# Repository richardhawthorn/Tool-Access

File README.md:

### Features

- Particle Photon
- 10A relay
- Current sensing
- RTC with battery backup
- Temperature input
- 3 x external inputs
- RFID reader connector
- 3.3V operation
- Onboard transformer 110v -> 5v

### License

This work is licensed under a Creative Commons Attribution-ShareAlike 4.0 International License.

<br />
Designed by <a xmlns:cc="http://creativecommons.org/ns#" href="http://www.richardhawthorn.com" property="cc:attributionName" rel="cc:attributionURL" target="_blank">Richard Hawthorn</a><br />
<a rel="license" href="http://creativecommons.org/licenses/by-sa/4.0/" target="_blank">View License</a>

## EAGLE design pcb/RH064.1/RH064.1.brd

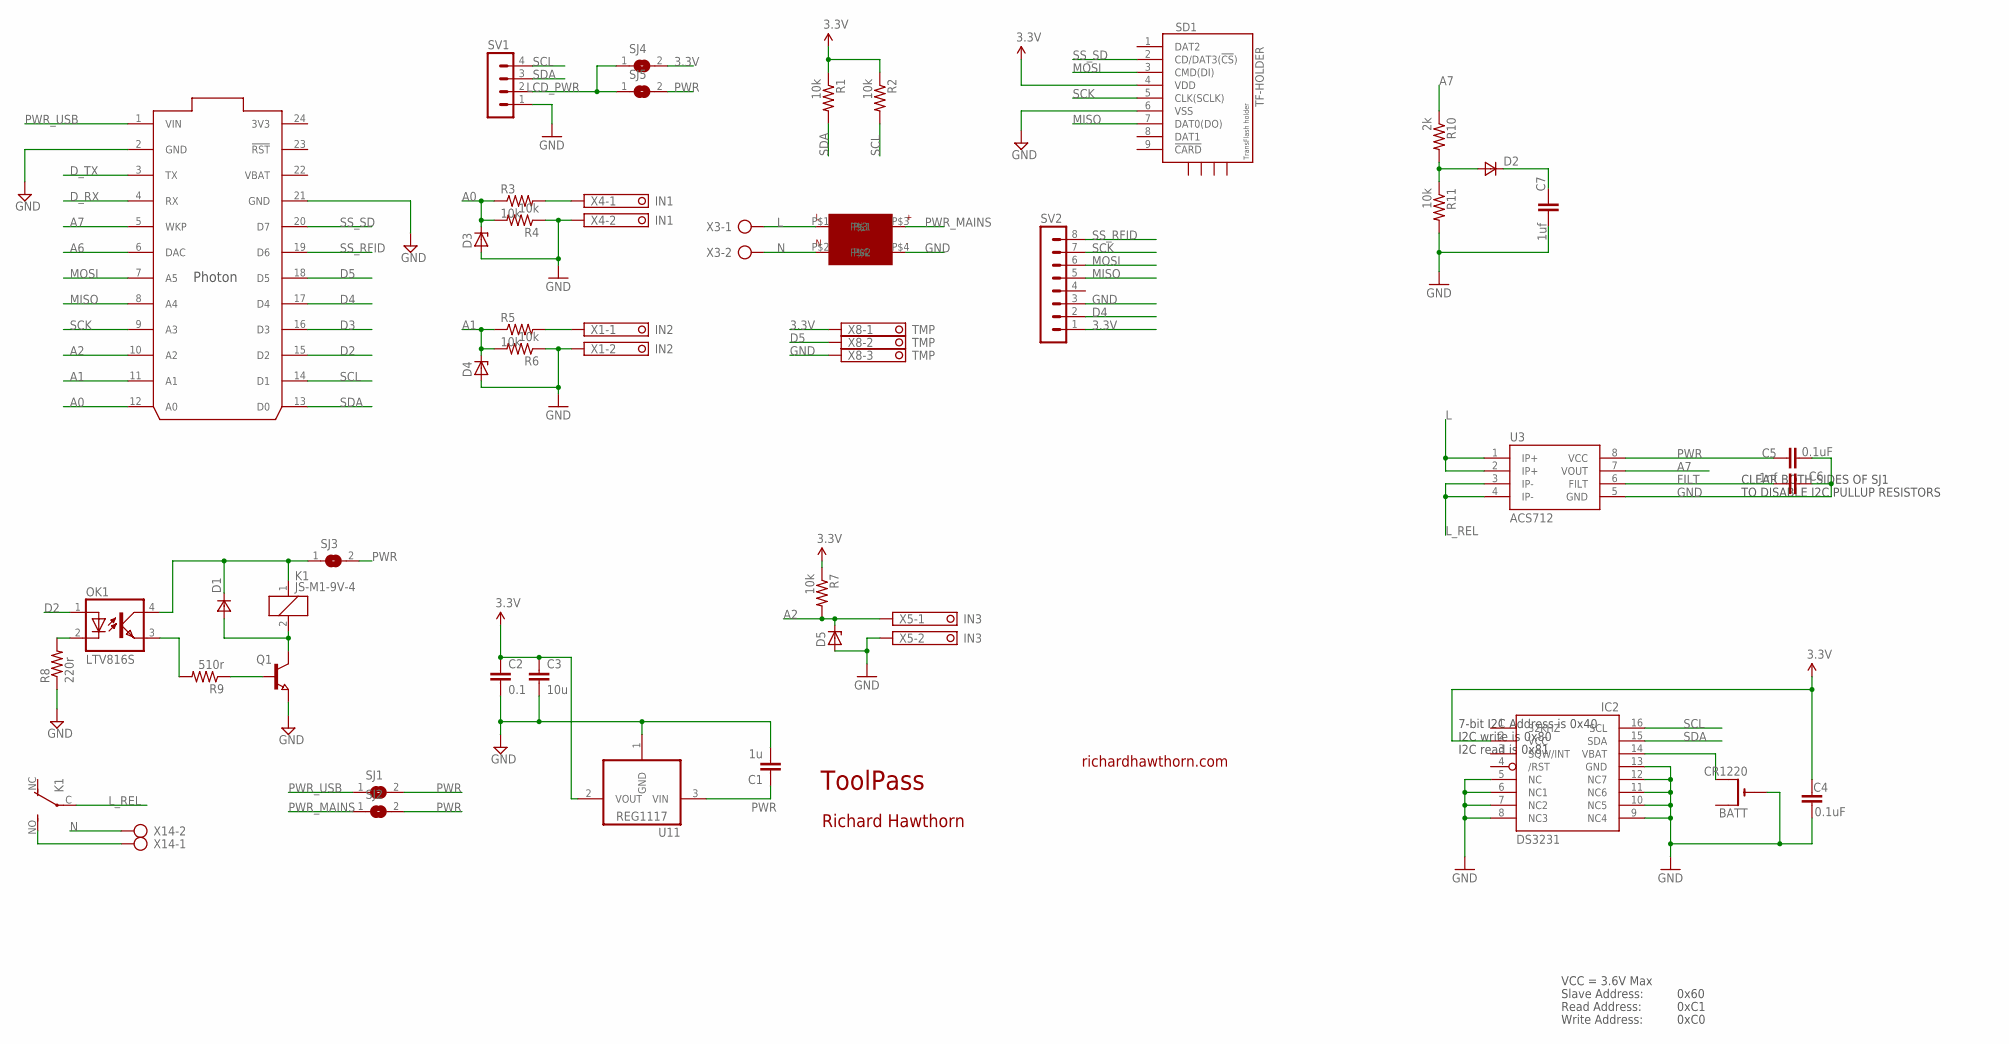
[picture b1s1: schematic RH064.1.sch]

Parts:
BATT: CR1220; CR1220-SMD
C1: 1u; 0603-CAP
C2: 0.1; 0603-CAP
C3: 10u; 0805-CAP
C4, C5: 0.1uF; 0603-CAP
C6: 1nf; 0603-CAP
C7: 1uf; 0603-CAP
D1, D2: VAR2SOT23; SOT-23
D3, D4, D5: ZENER-DIODESOT23; SOT23
IC2: DS3231; SO16W
K1: JS-M1-9V-4; JS-M
OK1: LTV816S; SMD4
Q1: NPN-TRANSISTOR_SOT23; SOT23
R1, R2, R11: 10k; 0805
R3, R4, R5, R6, R7: 10k; 0603-RES
R8: 220r; 0603-RES
R9: 510r; 0603-RES
R10: 2k; 0805
SD1: TF-HOLDER; TF-PULL
SJ1, SJ2, SJ3, SJ4, SJ5: SJ
SV1: MA04-1
SV2: MA08-1
U1: PHOTON_SMD
U3: ACS712; SO08
U11: REG1117; SOT223
U$1: 5VPWR
X1: IN2; 1751248
X3, X14: AK500/2
X4: IN1; 1751248
X5: IN3; 1751248
X8: TMP; 1751251

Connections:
3.3V: C2.1, C3.1, C4.1, IC2.2 (VCC), R1.1, R2.1, R7.1, SD1.4 (VDD), SJ4.2, SV2.1, U11.2 (VOUT), X8.1
3V3: U1.24 (3V3)
A0: D3.3 (C), R3.1, R4.2, U1.12 (A0)
A1: D4.3 (C), R5.1, R6.2, U1.11 (A1)
A2: D5.3 (C), R7.2, U1.10 (A2), X5.1
A6: U1.6 (DAC)
A7: R10.1, U1.5 (WKP), U3.7 (VOUT)
D2: OK1.1 (A), U1.15 (D2)
D3: U1.16 (D3)
D4: SV2.2, U1.17 (D4)
D5: U1.18 (D5), X8.2
D_RX: U1.4 (RX)
D_TX: U1.3 (TX)
FILT: C6.2, U3.6 (FILT)
GND: BATT.-, C1.2, C2.2, C3.2, C4.2, C5.2, C6.1, C7.2, D3.1 (A), D4.1 (A), D5.1 (A), IC2.5 (NC), IC2.6 (NC1), IC2.7 (NC2), IC2.8 (NC3), IC2.9 (NC4), IC2.10 (NC5), IC2.11 (NC6), IC2.12 (NC7), IC2.13 (GND), Q1.2 (E), R4.1, R6.1, R8.1, R11.2, SD1.6 (VSS), SV1.1, SV2.3, U1.2 (GND), U1.21 (GND), U3.5 (GND), U11.1 (GND), U$1.P$4, X1.2, X4.2, X5.2, X8.3
L: U3.1 (IP+), U3.2 (IP+), U$1.P$1, X3.1
LCD_PWR: SJ4.1, SJ5.1, SV1.2
L_REL: K1.C, U3.3 (IP-), U3.4 (IP-)
MISO: SD1.7 (DAT0(DO)), SV2.5, U1.8 (A4)
MOSI: SD1.3 (CMD(DI)), SV2.6, U1.7 (A5)
N: U$1.P$2, X3.2, X14.2
unnamed: OK1.3 (EMIT), R9.2
unnamed: R5.2, X1.1
unnamed: OK1.2 (C), R8.2
unnamed: K1.NO (S), X14.1
unnamed: R3.2, X4.1
unnamed: Q1.1 (B), R9.1
unnamed: D1.3 (A), K1.2, Q1.3 (C)
unnamed: BATT.+$2 (+1), IC2.14 (VBAT)
unnamed: D2.3 (A), R10.2, R11.1
unnamed: C7.1, D2.1 (C)
PWR: C1.1, C5.1, SJ1.2, SJ2.2, SJ3.2, SJ5.2, U3.8 (VCC), U11.3 (VIN)
PWR_MAINS: SJ2.1, U$1.P$3
PWR_USB: SJ1.1, U1.1 (VIN)
RL_PWR: D1.1 (C), K1.1, OK1.4 (COL), SJ3.1
SCK: SD1.5 (CLK(SCLK)), SV2.7, U1.9 (A3)
SCL: IC2.16 (SCL), R2.2, SV1.4, U1.14 (D1)
SDA: IC2.15 (SDA), R1.2, SV1.3, U1.13 (D0)
SS_RFID: SV2.8, U1.19 (D6)
SS_SD: SD1.2 (CD/DAT3(!CS!)), U1.20 (D7)
VBAT: U1.22 (VBAT)

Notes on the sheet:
ToolPass
richardhawthorn.com
Richard Hawthorn
CLEAR BOTH SIDES OF SJ1
TO DISABLE I2C PULLUP RESISTORS
7-bit I2C Address is 0x40
I2C write is 0x80
I2C read is 0x81
VCC = 3.6V Max
Read Address:
Write Address:
Slave Address:
0x60
0xC1
0xC0

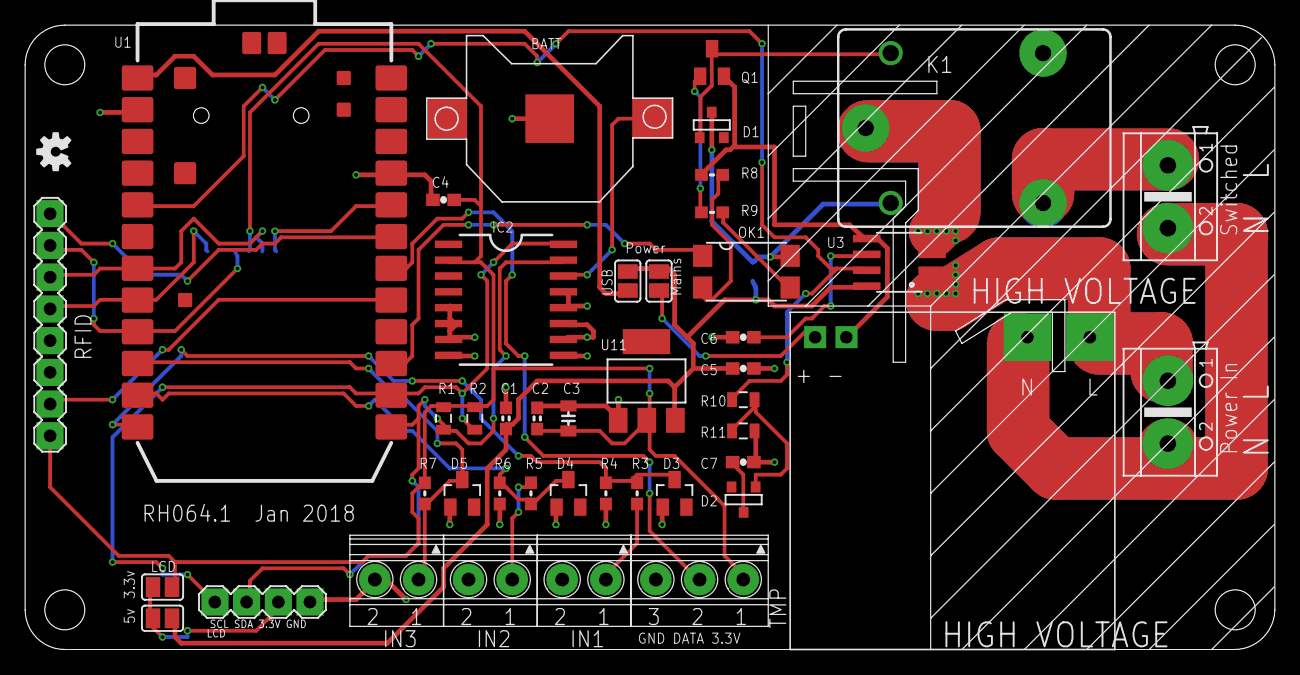
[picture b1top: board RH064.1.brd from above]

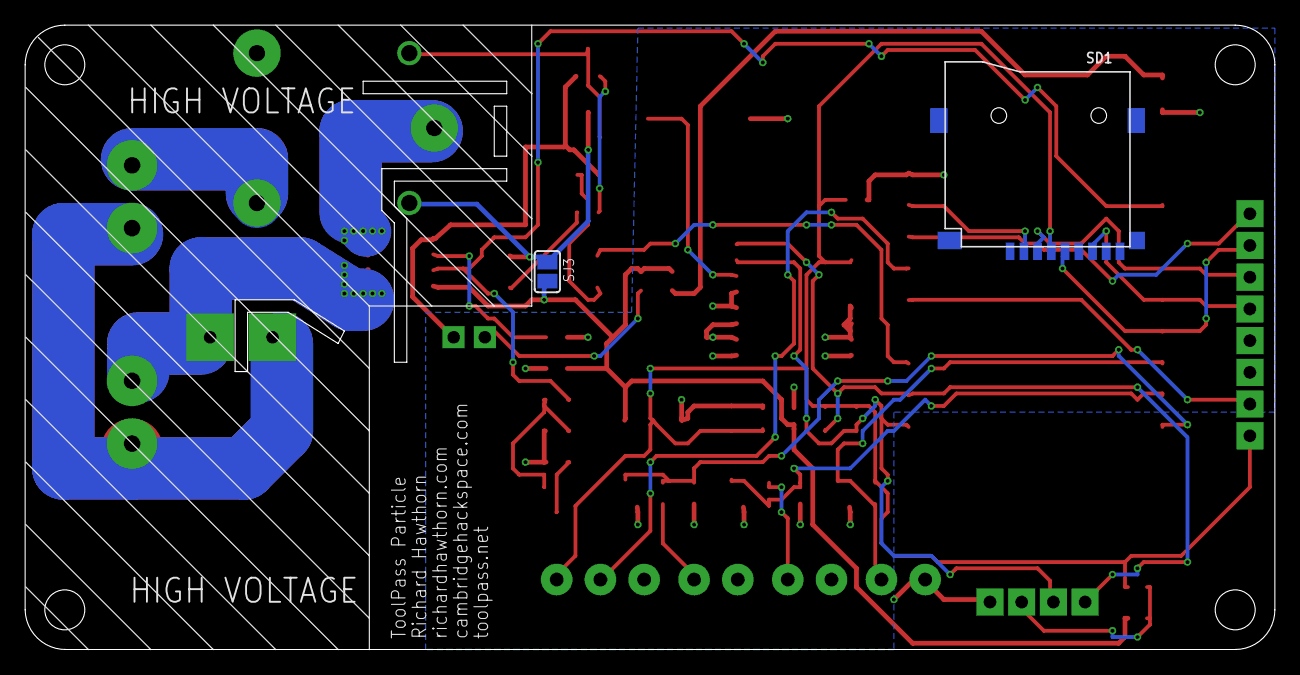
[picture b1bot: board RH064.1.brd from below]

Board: 2 copper layers, 100.1 x 50.0 mm, 47 parts (2 on the bottom side), 35 nets.

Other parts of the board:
U$3: OSHW-LOGO-S

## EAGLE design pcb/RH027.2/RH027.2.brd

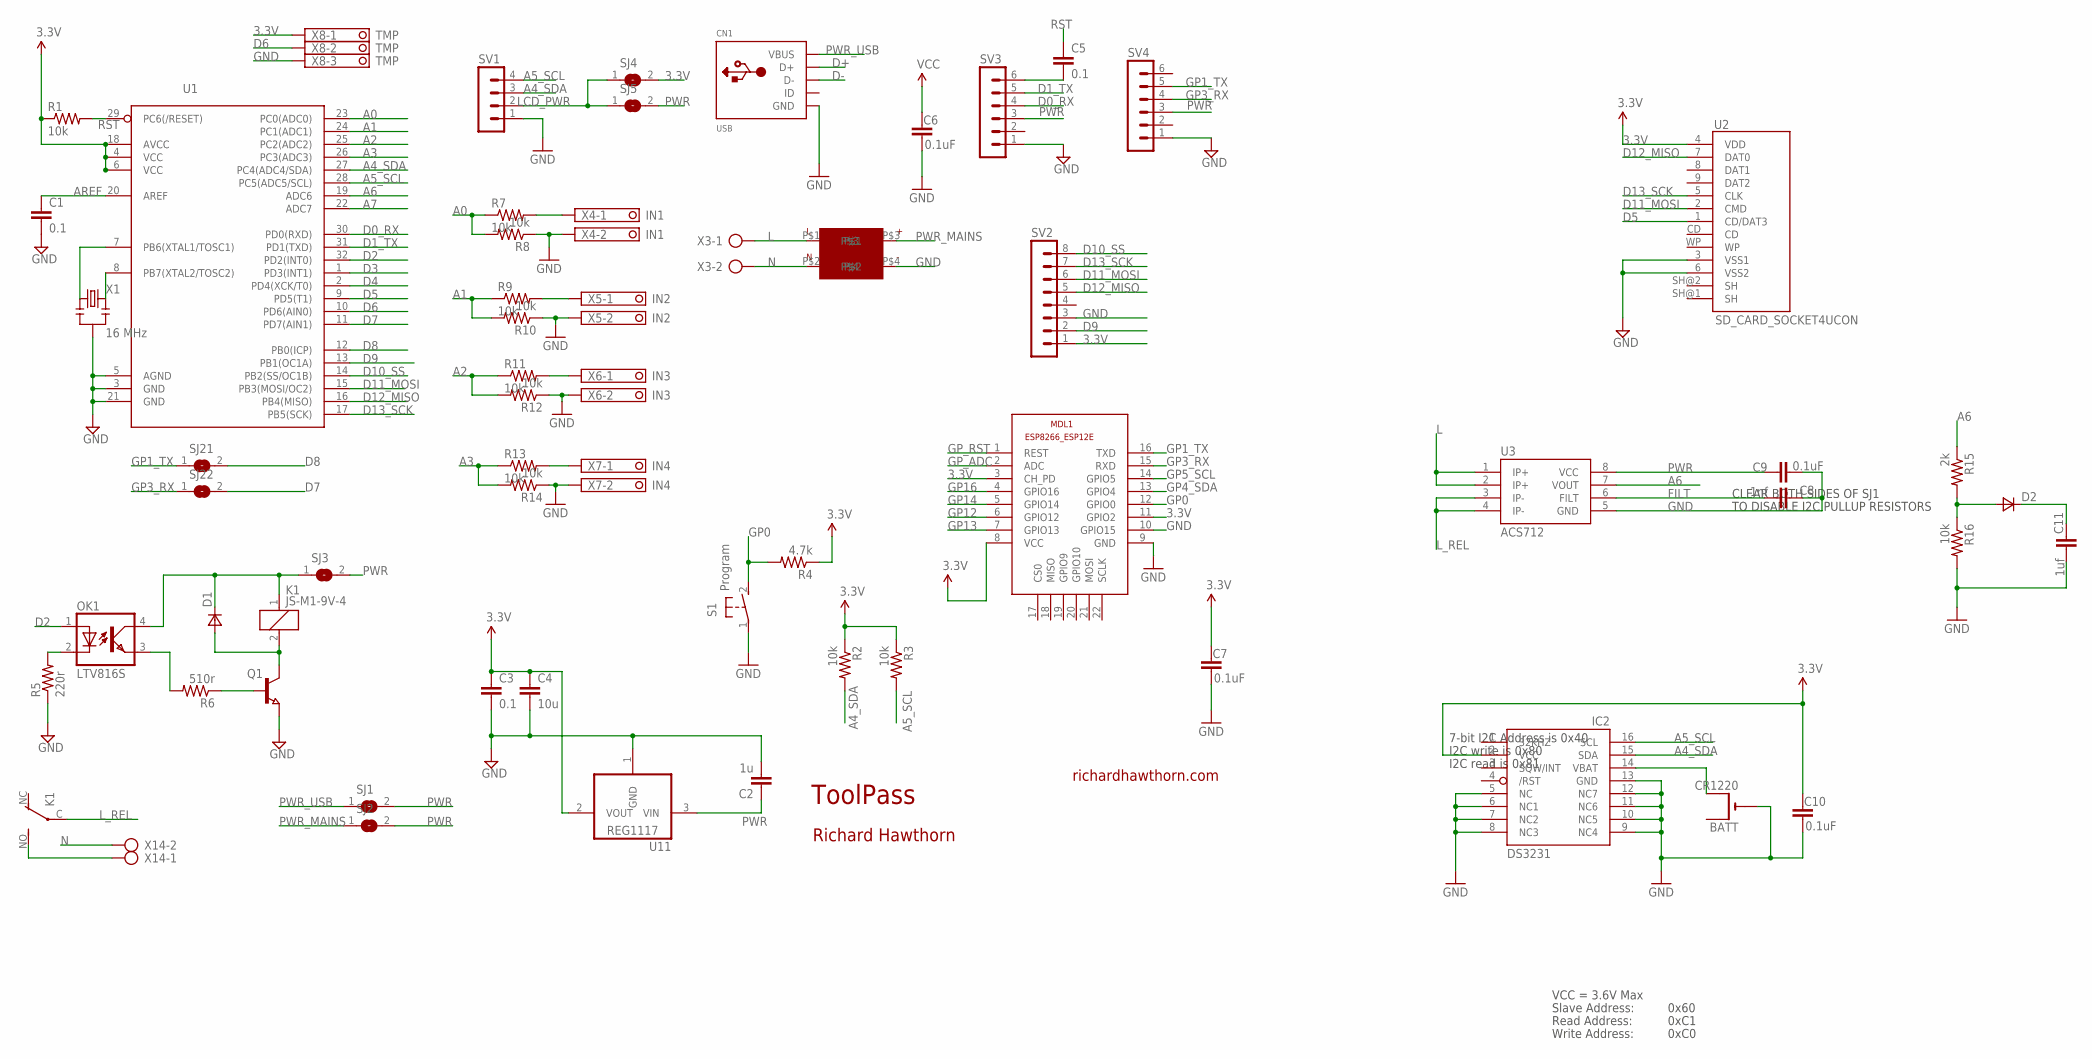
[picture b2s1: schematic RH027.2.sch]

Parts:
BATT: CR1220; CR1220-SMD
C1, C3, C5: 0.1; 0603-CAP
C2: 1u; 0603-CAP
C4: 10u; 0805-CAP
C6, C7, C9, C10: 0.1uF; 0603-CAP
C8: 1nf; 0603-CAP
C11: 1uf; 0603-CAP
CN1: USB; USB-MINIB
D1, D2: VAR2SOT23; SOT-23
IC2: DS3231; SO16W
K1: JS-M1-9V-4; JS-M
MDL1: ESP8266-12EESP8266-ESP12E; ESP8266-ESP12E
OK1: LTV816S; SMD4
Q1: NPN-TRANSISTOR_SOT23; SOT23
R1, R7, R8, R9, R10, R11, R12, R13, R14: 10k; 0603-RES
R2, R3, R16: 10k; 0805
R4: 4.7k; 0805
R5: 220r; 0603-RES
R6: 510r; 0603-RES
R15: 2k; 0805
S1: Program; DTSM-3
SJ1, SJ2, SJ3, SJ4, SJ5, SJ21, SJ22: SJ
SV1: MA04-1
SV2: MA08-1
SV3, SV4: MA06-1
U1: ATMega-328; TQFP32-08
U2: SD_CARD_SOCKET4UCON; SDCARD_4UCONN
U3: ACS712; SO08
U11: REG1117; SOT223
U$1: 5VPWR
X1: 16 MHz; RESONATOR-SMD
X3, X14: AK500/2
X4: IN1; 1751248
X5: IN2; 1751248
X6: IN3; 1751248
X7: IN4; 1751248
X8: TMP; 1751251

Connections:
3.3V: C3.1, C4.1, C6.1, C7.1, C10.1, IC2.2 (VCC), MDL1.3 (CH_PD), MDL1.8 (VCC), MDL1.11 (GPIO2), R1.1, R2.1, R3.1, R4.1, SJ4.2, SV2.1, U1.4 (VCC), U1.6 (VCC), U1.18 (AVCC), U2.4 (VDD), U11.2 (VOUT), X8.1
A0: R7.1, R8.2, U1.23 (PC0(ADC0))
A1: R9.1, R10.2, U1.24 (PC1(ADC1))
A2: R11.1, R12.2, U1.25 (PC2(ADC2))
A3: R13.1, R14.2, U1.26 (PC3(ADC3))
A4_SDA: IC2.15 (SDA), R2.2, SV1.3, U1.27 (PC4(ADC4/SDA))
A5_SCL: IC2.16 (SCL), R3.2, SV1.4, U1.28 (PC5(ADC5/SCL))
A6: R15.1, U1.19 (ADC6), U3.7 (VOUT)
A7: U1.22 (ADC7)
AREF: C1.1, U1.20 (AREF)
D0_RX: SV3.4, U1.30 (PD0(RXD))
D1_TX: SV3.5, U1.31 (PD1(TXD))
D2: OK1.1 (A), U1.32 (PD2(INT0))
D3: U1.1 (PD3(INT1))
D4: U1.2 (PD4(XCK/T0))
D5: U1.9 (PD5(T1)), U2.1 (CD/DAT3)
D6: U1.10 (PD6(AIN0)), X8.2
D7: SJ22.2, U1.11 (PD7(AIN1))
D8: SJ21.2, U1.12 (PB0(ICP))
D9: SV2.2, U1.13 (PB1(OC1A))
D10_SS: SV2.8, U1.14 (PB2(SS/OC1B))
D11_MOSI: SV2.6, U1.15 (PB3(MOSI/OC2)), U2.2 (CMD)
D12_MISO: SV2.5, U1.16 (PB4(MISO)), U2.7 (DAT0)
D13_SCK: SV2.7, U1.17 (PB5(SCK)), U2.5 (CLK)
D+: CN1.D+
D-: CN1.D-
FILT: C8.2, U3.6 (FILT)
GND: BATT.-, C1.2, C2.2, C3.2, C4.2, C6.2, C7.2, C8.1, C9.2, C10.2, C11.2, CN1.GND, IC2.5 (NC), IC2.6 (NC1), IC2.7 (NC2), IC2.8 (NC3), IC2.9 (NC4), IC2.10 (NC5), IC2.11 (NC6), IC2.12 (NC7), IC2.13 (GND), MDL1.9 (GND), MDL1.10 (GPIO15), Q1.2 (E), R5.1, R8.1, R10.1, R12.1, R14.1, R16.2, S1.1, SV1.1, SV2.3, SV3.1, SV4.1, U1.3 (GND), U1.5 (AGND), U1.21 (GND), U2.3 (VSS1), U2.6 (VSS2), U3.5 (GND), U11.1 (GND), U$1.P$4, X1.2, X4.2, X5.2, X6.2, X7.2, X8.3
GP0: MDL1.12 (GPIO0), R4.2, S1.2
GP1_TX: MDL1.16 (TXD), SJ21.1, SV4.5
GP3_RX: MDL1.15 (RXD), SJ22.1, SV4.4
GP4_SDA: MDL1.13 (GPIO4)
GP5_SCL: MDL1.14 (GPIO5)
GP12: MDL1.6 (GPIO12)
GP13: MDL1.7 (GPIO13)
GP14: MDL1.5 (GPIO14)
GP16: MDL1.4 (GPIO16)
GP_ADC: MDL1.2 (ADC)
GP_RST: MDL1.1 (REST)
L: U3.1 (IP+), U3.2 (IP+), U$1.P$1, X3.1
LCD_PWR: SJ4.1, SJ5.1, SV1.2
L_REL: K1.C, U3.3 (IP-), U3.4 (IP-)
N: U$1.P$2, X3.2, X14.2
unnamed: OK1.3 (EMIT), R6.2
unnamed: U1.7 (PB6(XTAL1/TOSC1)), X1.1
unnamed: OK1.2 (C), R5.2
unnamed: K1.NO (S), X14.1
unnamed: R9.2, X5.1
unnamed: R7.2, X4.1
unnamed: R11.2, X6.1
unnamed: R13.2, X7.1
unnamed: C5.2, SV3.6
unnamed: U1.8 (PB7(XTAL2/TOSC2)), X1.3
unnamed: Q1.1 (B), R6.1
unnamed: D1.3 (A), K1.2, Q1.3 (C)
unnamed: BATT.+$2 (+1), IC2.14 (VBAT)
unnamed: D2.3 (A), R15.2, R16.1
unnamed: C11.1, D2.1 (C)
PWR: C2.1, C9.1, SJ1.2, SJ2.2, SJ3.2, SJ5.2, SV3.3, SV4.3, U3.8 (VCC), U11.3 (VIN)
PWR_MAINS: SJ2.1, U$1.P$3
PWR_USB: CN1.VBUS, SJ1.1
RL_PWR: D1.1 (C), K1.1, OK1.4 (COL), SJ3.1
RST: C5.1, R1.2, U1.29 (PC6(/RESET))

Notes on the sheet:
ToolPass
richardhawthorn.com
Richard Hawthorn
CLEAR BOTH SIDES OF SJ1
TO DISABLE I2C PULLUP RESISTORS
7-bit I2C Address is 0x40
I2C write is 0x80
I2C read is 0x81
VCC = 3.6V Max
Read Address:
Write Address:
Slave Address:
0x60
0xC1
0xC0

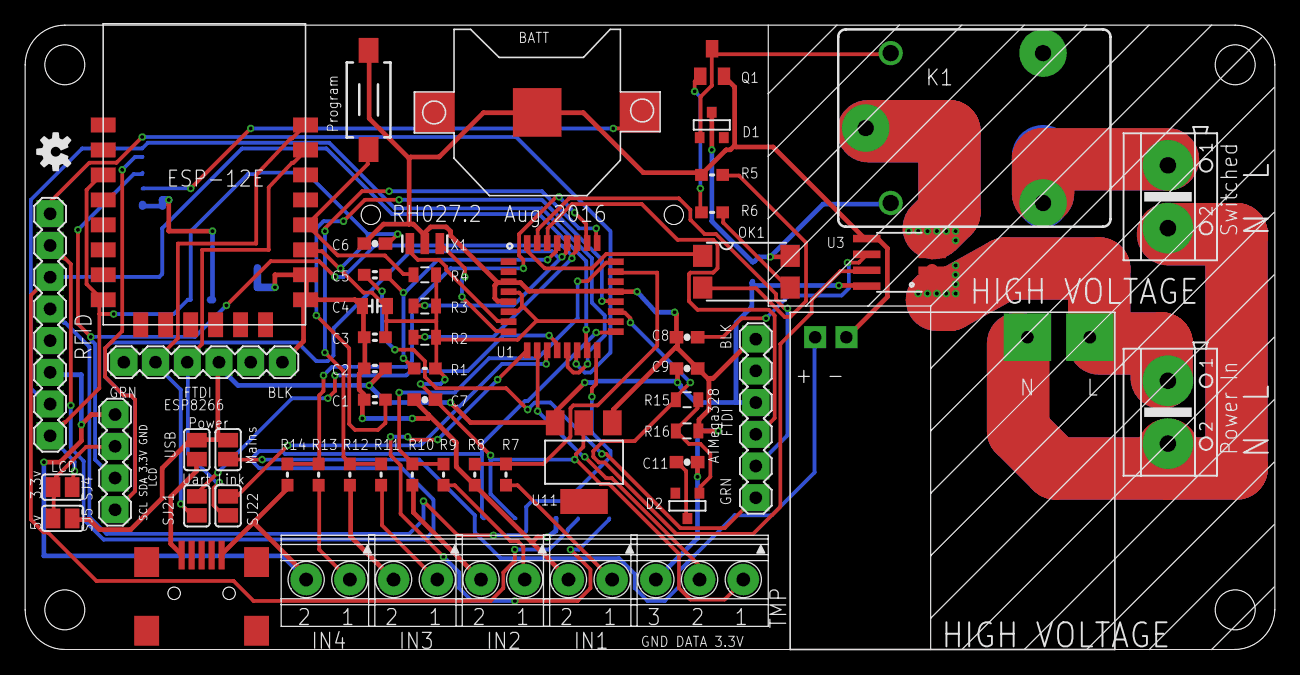
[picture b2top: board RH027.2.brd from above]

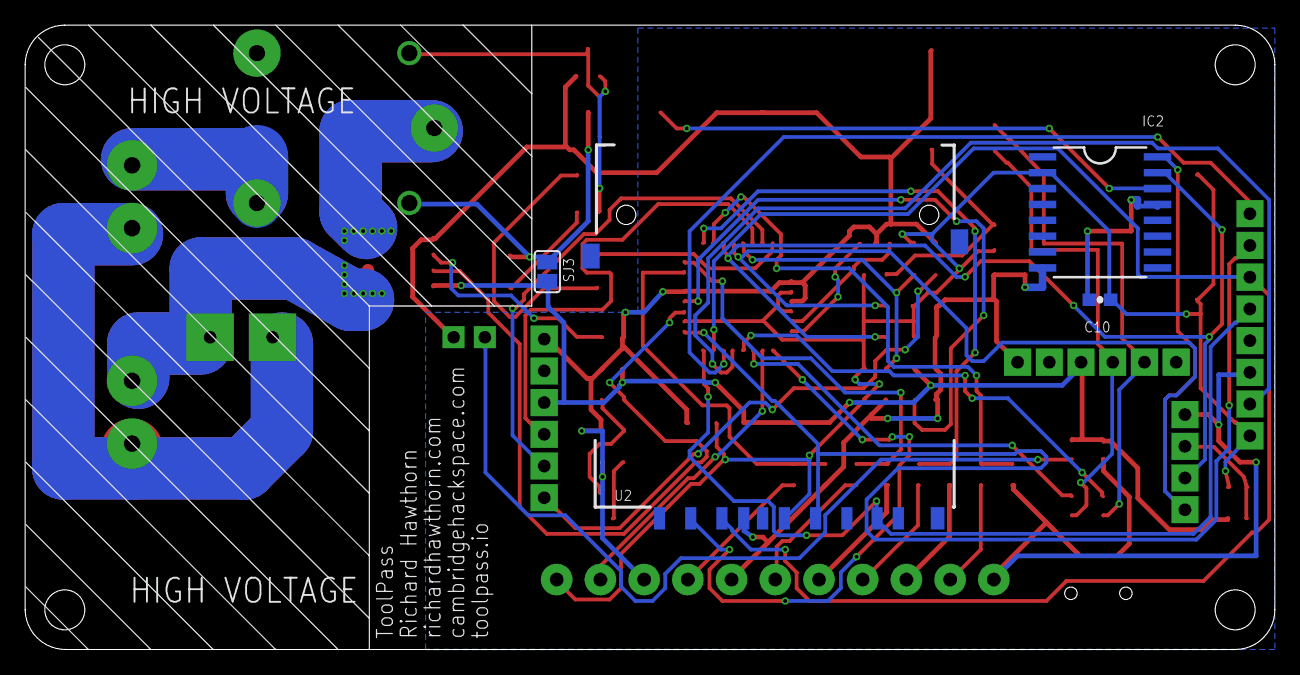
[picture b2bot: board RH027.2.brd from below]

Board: 2 copper layers, 100.1 x 50.0 mm, 62 parts (4 on the bottom side), 50 nets.

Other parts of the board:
U$3: OSHW-LOGO-S

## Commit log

2016-11-08 adding the pcb files
2016-11-08 adding pcb v2
2016-11-08 add readme
2018-01-29 add new boards and images
2018-01-29 update images

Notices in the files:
parts and their libraries:
SparkFun-Aesthetics: Licensing: CC v3.0 Share-Alike You are welcome to use this library for commercial purposes.
SparkFun-Connectors: Licensing: Creative Commons ShareAlike 4.0 International - https://creativecommons.org/licenses/by-sa/4.0
